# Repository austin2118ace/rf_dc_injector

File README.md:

# RF DC Injector

This repository hosts a simple PCB for a RF DC injector/extractor for use in HAM radio applications.

## Brief Description
DC can be co-located on a RF feed line to power remote hardware with only two of these boards. On the injector side, the DC power supply is protected from the RF with a bank of inductors, and the RF power source is isolated from the DC using a capacitor.
On the "extractor" side, the same board is used in the reverse configuration. The antenna is isolated from the DC using the capacitor, and the remote DC power rail is isolated from RF using the inductors.

## Manufacturing
I had several of these boards manufactured at Oshpark but JLCPCB/PCBWay are both valid options. There are two pads for coax connections; I used two lengths of RG316. For the DC power input/output, there is a footprint for a standard DC power jack.
Choose value(s) of capacitance and inductance that make sense for your application.

## Compatability
This project was created using KiCad v10 and includes a custom footprint that you will need to ensure is correctly loaded. 

Good luck and 73!
KQ4TYW

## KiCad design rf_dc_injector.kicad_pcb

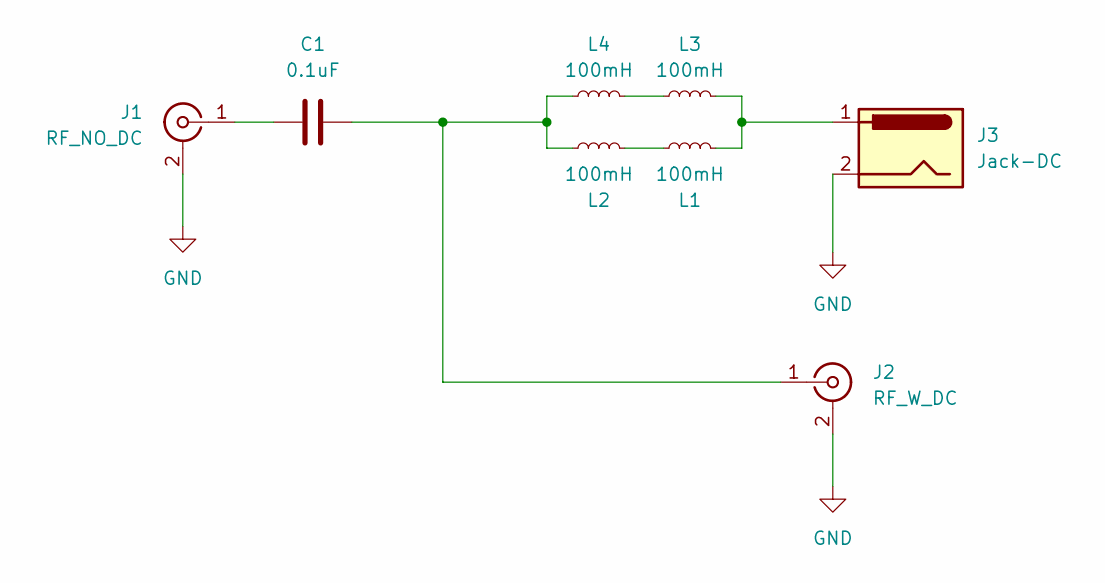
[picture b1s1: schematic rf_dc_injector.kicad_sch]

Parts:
C1: 0.1uF; C_Rect_L11.0mm_W3.4mm_P10.00mm_MKT
J1: RF_NO_DC; RG-316-Through-Hole
J2: RF_W_DC; RG-316-Through-Hole
J3: Jack-DC; BarrelJack_Horizontal
L1, L2, L3, L4: 100mH; L_Axial_L6.6mm_D2.7mm_P10.16mm_Horizontal_Vishay_IM-2

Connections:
GND: J1.2 (Ext), J2.2 (Ext), J3.2
unnamed: C1.1, J1.1 (In)
unnamed: C1.2, J2.1 (In), L2.1, L4.1
unnamed: J3.1, L1.2, L3.2
unnamed: L3.1, L4.2
unnamed: L1.1, L2.2

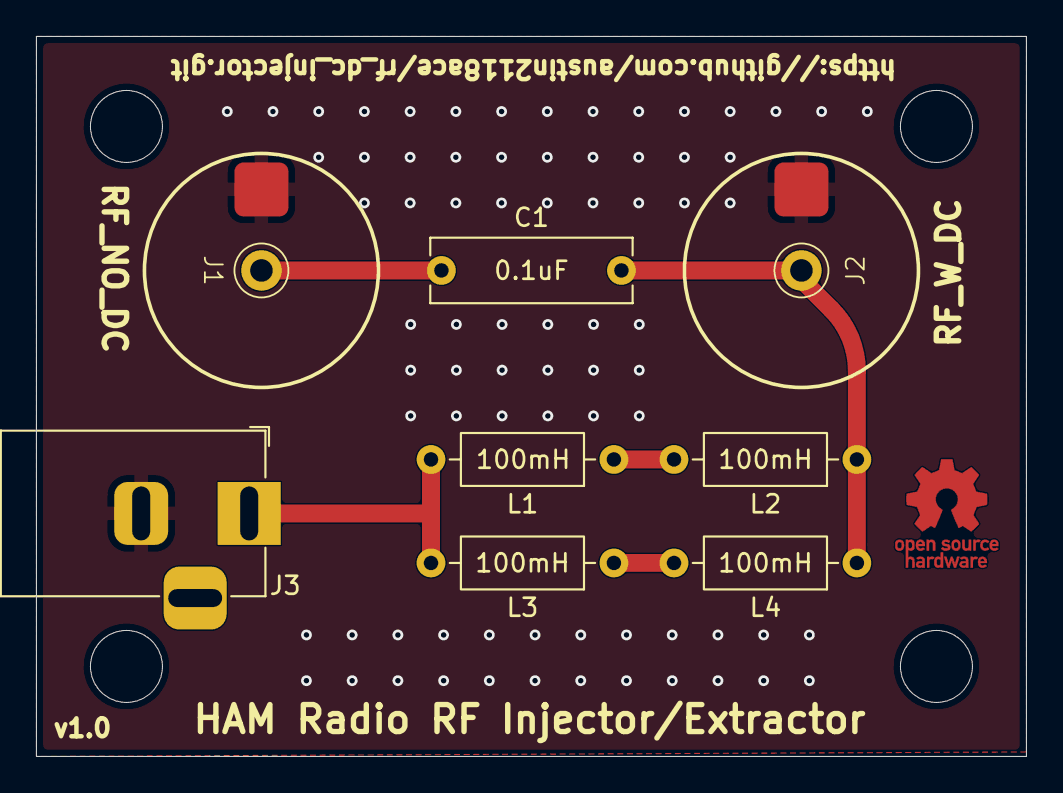
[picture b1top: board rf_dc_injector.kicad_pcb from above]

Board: 2 copper layers, 55.0 x 40.0 mm, 8 parts (0 on the bottom side), 6 nets.
